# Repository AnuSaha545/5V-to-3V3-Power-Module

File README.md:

# 5V to 3.3V Power Module

A compact linear power supply module designed using **KiCad** to convert **5V input to a stable 3.3V output**.  
This project covers the complete PCB design workflow — from schematic capture to PCB layout, routing, and Gerber generation for fabrication.

---

## 🔧 Features

- Converts **5V DC input to regulated 3.3V output**
- Based on **AMS1117-3.3** linear voltage regulator
- Input and output via **screw terminal / pin header**
- Includes input/output decoupling capacitors for stability
- Power indication LED with current-limiting resistor
- Compact single-layer PCB layout
- Fabrication-ready Gerber and drill files included

---

## 📐 Schematic

The schematic was designed in KiCad following standard power supply design practices, including proper decoupling and grounding.

> *(See schematic file in repository)*  
`5V_to_3V3_Power_Module.kicad_sch`

---

## 🧩 PCB Layout

- Fully routed PCB with labeled connectors
- Clear silkscreen markings for **VIN, GND, VOUT**
- Ground copper fill for improved performance
- Designed as **Rev 1.0**

### PCB Views

#### Schematic

#### Top View

#### Annotated PCB Layout

#### 3D View

---

## 🏭 Manufacturing Files

All fabrication-ready files are provided.

📁 **gerbers/**
- Copper layers
- Silkscreen
- Solder mask
- Board outline (Edge.Cuts)
- Drill files (PTH / NPTH)

These Gerbers can be directly uploaded to PCB manufacturers such as **JLCPCB**, **PCBWay**, or **Seeed Studio**.

---

## 🛠 Tools Used

- **KiCad 8.0**
- Git & GitHub for version control

---

## 👩‍💻 Designed By

**Anu Saha**  
Electronics & Telecommunication Engineering  
PCB Design | KiCad | Hardware Projects

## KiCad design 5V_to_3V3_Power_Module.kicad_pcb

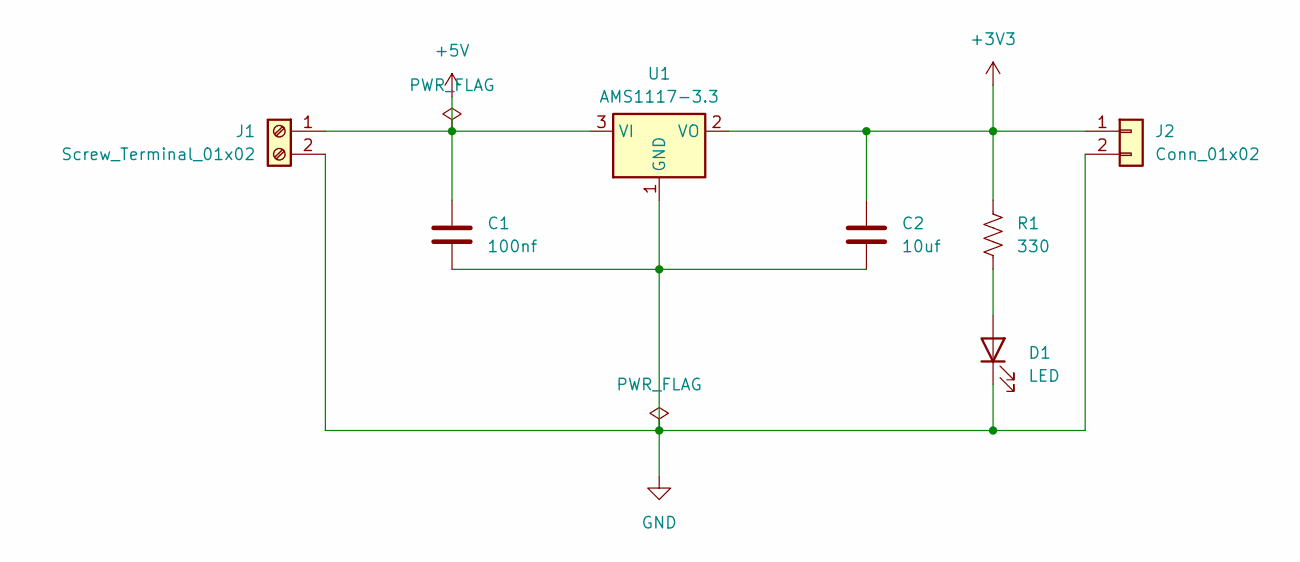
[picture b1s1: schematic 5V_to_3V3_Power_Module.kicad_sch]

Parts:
C1: 100nf; C_0805_2012Metric
C2: 10uf; C_0805_2012Metric
D1: LED; LED_0805_2012Metric
J1: Screw_Terminal_01x02; TerminalBlock_bornier-2_P5.08mm
J2: Conn_01x02; PinSocket_1x02_P2.54mm_Vertical
R1: 330; R_0805_2012Metric
U1: AMS1117-3.3; SOT-223-3_TabPin2

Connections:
+3V3: C2.1, J2.1, R1.1, U1.2 (VO)
+5V: C1.1, J1.1, U1.3 (VI)
GND: C1.2, C2.2, D1.1 (K), J1.2, J2.2, U1.1 (GND)
unnamed: D1.2 (A), R1.2

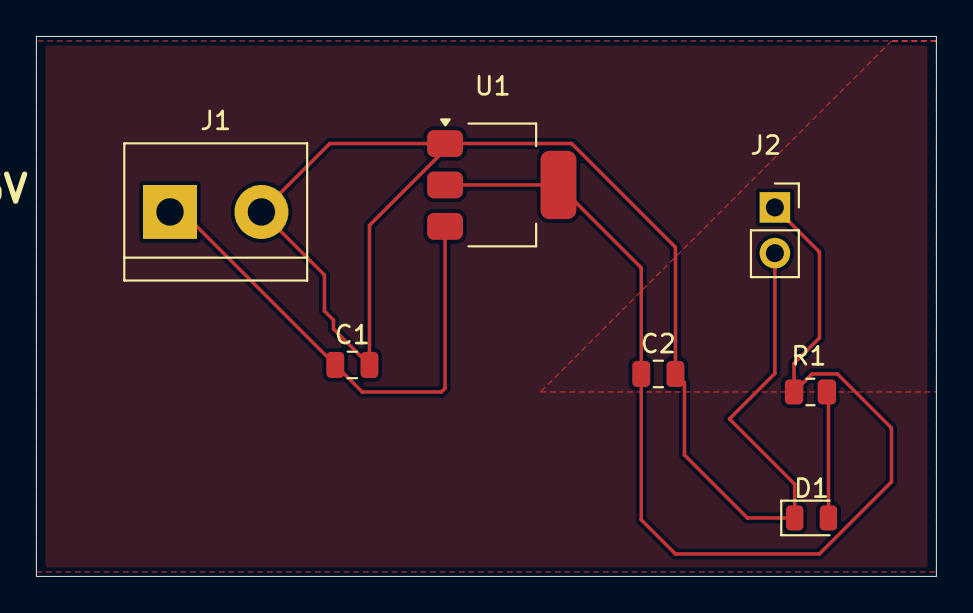
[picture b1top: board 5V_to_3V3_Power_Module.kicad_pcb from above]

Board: 2 copper layers, 50.0 x 30.0 mm, 7 parts (0 on the bottom side), 4 nets.

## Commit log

2026-01-17 Add 5V to 3.3V power module KiCad design, gerbers, and documentation images
2026-01-17 Add README for 5V to 3.3V Power Module project
    Added detailed project information for the 5V to 3.3V Power Module, including features, schematic, PCB layout, manufacturing files, tools used, and designer information.
